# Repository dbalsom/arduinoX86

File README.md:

### About ArduinoX86

I've written a blog article that gives an overview of this project and how it is used.

https://martypc.blogspot.com/2023/06/hardware-validating-emulator.html

This project was originally called Arduino8088, but then I expanded it to support the 8086, 80186, 80286, with plans for
the 80386, so it is now named the suitably generic ArduinoX86.

### Description

This project expands on the basic idea of controlling a CPU via GPIO pins to clock the CPU and read and write control
and data signals. This can be used to validate an emulator's accuracy, but also as a general method of exploring the
operation of CPU instructions and timings.

This project currently supports the following CPUs:

- CMOS variants of the 8088 (Oki, Harris 80C88, etc.)
- AMD D8088
- CMOS variants of the 8086 (Intel 80C86, Harris 80C86)
- NEC V20
- NEC V30
- Intel 80L186
- Harris 80C286
- Intel 80386EX

Where it differs from existing Raspberry Pi-based projects is that it uses an Arduino Giga for the expanded number of
GPIO pins available. The Giga has enough GPIO to operate 808X-compatible CPUs in Maximum mode. This enables several
useful signals to be read such as the QS0 & QS1 processor instruction queue status lines, which give us more insight
into the internal state of the CPU. We can also enable inputs such as READY, NMI, INTR, and TEST, so we can execute
interrupts, NMIs, emulate wait states, and potentially even simulate FPU and DMA operations.

I have been using this project to validate the cycle-accuracy of my PC
emulator, [MartyPC](https://github.com/dbalsom/martypc), and produce CPU test
suites for emulators, covering
the [8088](https://github.com/singleStepTests/8088/), [V20](https://github.com/SingleStepTests/v20)
and [8086](https://github.com/singleStepTests/8086/) and [286](https://github.com/singlesteptests/80286) to date.

This project has three main components:

- The CPU server software, which runs on the Arduino, and establishes a serial protocol to reset the CPU, load and store
  register state, as well as interactively operate the CPU if desired;
- The CPU client software, which runs on your computer and controls the CPU after the CPU server has set up initial
  register state as desired, or uploads an entire program to be run automatically with register state collected at the
  end of execution;
- The CPU socket PCB shields, which seat on top of the Arduino, and provide a physical interface between the CPU and
  GPIO
  lines.

The original "Arduino8088" project utilized an Arduino MEGA, but this board no longer supported.
It is painfully slow and limited to a serial UART instead of fast native USB communication. As of the current
release, an [Arduino Due](https://store.arduino.cc/products/arduino-due), or preferably,
an [Arduino GIGA](https://store.arduino.cc/products/giga-r1-wifi) should be used instead. A GIGA is required to
operate 5V CPUs such as older 80186's and the 80286. Despite Arduino's official warnings, the STM32 GPIO in the Giga is
5V tolerant (with a few exceptions). You will likely void your warranty and I take no responsibility for any damage to
your Arduino that occurs attempting to use a 5V CPU with your Arduino.

### 8088,8086,V20,V30 Support

Revision 1.1 of the 808X shield supports the 8086 and NEC V30 by adding a connection for the 8086's BHE pin.

The Due can operate the 8088, 8086, V20 and V30, despite these chips being 5V. The current 8088 shield feeds those CPUs
3.3V which they tolerate quite well at low clock speeds.

The Giga can operate the 8088, 8086, V20 and V30 directly at 5V if desired. The Giga requires the 3V supply pin to be
cut off the shield's pin headers and external power supplied due to the lower available overall power budget.

> [!WARNING]  
> Do not attempt to use the 8088 shield with a Giga without using external power, or you may damage your Arduino.

### 80186 Support

The ArduinoX86 cpu_server sketch supports operation of a low-voltage 80L186 on an Arduino Due.

There is no shield yet for the 80186, you will need to use a breakout board and connect directly to the Arduino Due's
headers. See [Using an 80186](https://github.com/dbalsom/arduinoX86/wiki/Using-an-80186) for more information.

### 80286 Support

A shield for the 80C286 is in the design phase, located in `/shields/286_5V`

Current support for the 80286 has been performed via breadboard.

### 80386 Support

A shield for the 80386EX CPU is provided in `/shields/386EX_V4`

## Can the CPU be clocked fast enough with an Arduino?

In short, no. We are well past the published minimum cycle times when executing programs via a serial protocol, cycle by
cycle. Some chips tolerate this better than others. When working with an Intel branded 8088, I noticed that effective
address calculations were failing to add the displacement or index register, but otherwise functioned. I have had more
luck with the AMD second-source 8088 CPUs, which seem to function perfectly under slow clocks, although they will hang
and need to be reset if not cycled for a several milliseconds. The issue is "dynamic logic" - logic gates that lose
their state if not refreshed electrically within a frequent enough interval. To be absolutely safe, it is best to use a
fully CMOS process CPU such as the 80C88. CMOS versions of most x86 chips are available.

## To use

An example application for cpu_server is provided, written in Rust, in the `/crates/exec_program` directory. It
demonstrates how to upload arbitrary code to the ArduinoX86 and display cycle traces. The client will emulate the
entire address space and set up a basic IVT.

# Project Structure

## /asm

Assembly language files, intended to be assembled with NASM. To execute code on the ArduinoX86, one must supply two
binary files, one containing the program to be executed, and one containing the register values to load onto the CPU
before program execution.

## /crates/arduinox86_client

A library crate that implements a client for the ArduinoX86's serial protocol.

## /crates/arduinox86_cpu

A library crate built on top of the `arduinox86_client` crate, this provides a `RemoteCpu` struct that models CPU state
and can execute programs.

## /crates/arduinox86_gui

A GUI (written in egui) for ArduinoX86, supporting the 386EX. It allows you to write and assemble assembly-language
programs and execute them on the CPU with an easy-to-use interface.

## /crates/exec_program

A binary implementing an interface for the `arduinox86_cpu` crate that will load a provided register state binary and
execute the specified program binary.

## /crates/test_generator

A program that generates CPU tests for emulator authors.

The [segment limit capture suite](crates/test_generator/SEGMENT_LIMITS.md) adds deterministic
286 and 386EX real and protected mode observations using the same CPU client and server.

### /shields

Contains the KiCad project files and Gerber files for the various ArduinoX86 shields. See the README.md in each shield
directory for more information and BOMs for building each.

### /platformio/ArduinoX86

The main server code that runs on the Arduino Due or GIGA. You must have [platformio](https://platformio.org/) installed
to build and upload the project to your Arduino.

## Archived Directories

### /sketches/cpu_server

The original cpu_server Arduino IDE sketch. Development has since moved to platformio.

### /sketches/run_program

The original sketch for Arduino MEGA only demonstrating how to control an 8088. It does not contain a serial protocol
server - code is run directly from an array defined within the sketch.

# Ordering Boards

- Ordering boards from any of the KiCad projects is extremely simple using PCBWay's KiCad fabrication plugin.
  - From the Plugin and Content Manager, go the Fabrication Plugins tab, find the PCBWay plugin and install.
  - 
  - Open the PCB editor and click the PCBWay Button
  - 
  - A browser window will open to PCBWay's website with the project uploaded and acceptable defaults selected.
  - If you like you can change the board color, or get a nicer finish with gold (ENIG).
  - 
  - You can then proceed to ordering. Part of your purchase goes back to help fund the KiCad project, which is cool.
  - 

# Credits

Inspired by the Pi8088 validator created by Andreas Jonsson as part of the VirtualXT project:

https://github.com/andreas-jonsson/virtualxt/tree/develop/tools/validator/pi8088

# Other Cool Projects

- 8bitforce's Retroshield: https://www.8bitforce.com/projects/retroshield/

- homebrew8088's Raspberry Pi Hat: https://github.com/homebrew8088/pi86

- The Universal Chip Analyser (U. C. A.): https://x86.fr/uca/

- Foxtech's 486 Breadboard Computer: https://www.youtube.com/watch?v=wSiDSdHS2QQ

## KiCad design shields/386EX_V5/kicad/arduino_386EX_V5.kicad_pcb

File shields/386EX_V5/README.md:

# ArduinoX86 386EX Shield V5

- This is the latest shield design for the 386EX CPU. It supports the addition of a 387SX FPU via stacking headers.

- The 386EX is a low-voltage variant of the 386 with a 16-bit data bus, intended for embedded applications.

- This shield is intended to be **only compatible with the Arduino GIGA board**.

### Important power-related notes:

- This shield has external power pins. You may connect a 3.3V or 5V power source to the pins, i.e. via 0.1" / 2.54mm "DuPont" connectors.

- You may find that the CPU runs even without external power. This is due to the CMOS process - many CMOS CPUs can power themselves by sinking current from any input pin. Correct operation in this state is not guaranteed and has not been battle-tested.

### Notes about 386EX CPUs:

- Unsoldered new-old-stock 386EX chips are often available on eBay, but your mileage may vary.

### Other notes:

If using a donor board, a hot plate or hot-air station will be necessary to successfully remove the CPU without damage.

This shield adds new features over the original:

- PEREQ and ERROR pins have been connected to support stacking a 387SX shield,
- The SMI and SMIACT pins have been connected,
- The JTAG pins have been replaced by a 2x4 header, in popular 0.1" / 2.54mm "DuPont" pins,
- The first Asynchronous serial port has been replaced by a 2x5 header (Serial0),
- The first 8 external INTR lines (INTR0-INTR7) have been run out to separate 1x4 headers,
- 7 status LEDs have been added that will report the status of SMIACT, ADS, RD, WR, W/R, C/M and M/IO.

### Improvements (v5.x) over the previous design (v4) include:

- Added ST LDL1117 1A voltage regulator for the 3.3V bus; this enables users to select from a 5V external power source, 5V input via Arduino pin headers, and 3.3V input via the JTAG/debug header.
- Migrated to 4-layer PCB, and migrated most serial and data traces to the 2x internal copper layers.
- Rounded PCB traces for improved data signal integrity.
- Resized silkscreen labels from 1.0mm to 0.8mm and improved layout.
- Improved schematic layout by grouping major components and subsystems together, for easier readability.
- Added standard diodes to protect 5V and 3.3V inputs and busses from accidental back-feeding.
- Added high-resolution renders of board front and back, populated and depopulated, for improved clarity in assembly diagrams.
- Added note about customizing LED current-limiting resistor values per their current and forward voltage.
- Added BOM to this README.
- Added interactive HTML BOM.
- Added schematic and PCB layout `.PDF` files.
- Added `/production` folder with ready-to-fabricate `.zip` file and `.csv` files for communicating with PCB fabrication houses.

### WARNING!
> Successfully assembling this board requires advanced soldering skills. A solder mask, solder paste, and a hot plate are recommended. (Or in a pinch, a high proficiency with drag-soldering techniques.)

### BOM

Note: Interactive HTML bill of materials is available in `./bom/ibom.html`.

| Reference | Value | Footprint | Quantity |
| --------- | ----- | --------- | -------- |
| C3, C4, C5, C6, C7, C8, C9, C10, C11, C12, C13, C14 | 0.1 µF | C_0603 | 12 |
| C1 | 4.7 µF | C_0805 | 1 |
| C2 | 1 µF | C_0805 | 1 |
| R2, R3, R4, R5, R9, R10, R11 | User's TBD | R_0603 | 7 |
| R1, R6, R7, R8, R12, R13, R14, R15 | 3.3 K Ω | R_0603 | 7 |
| D1, D2, D4, D5, D6, D7, D8 | 20mA green |  D_0603 | 7 |
| D3, D9, D10 | S1A-13-F | DIOM5226X240N | 3 |
| U1 | LDL1117S33R | SOT223_STM-M | 1 |
| U2 | ULN2003A | TSSOP-16_4.4x5mm_P0.65mm | 1 |
| U3 | SN74LV14A | TSSOP-14_4.4x5mm_P0.65mm | 1 |
| U4 | AT24CS01-STUM | SOT-23-5 | 1 |
| U5 | I386EX_PQFP | PQFP-132_24x24mm_P0.635mm_i386 | 1 |
| J5, J6, J7 | 4-pin DuPont | PinHeader_1x04_P2.54mm_Vertical | 3 |
| J1, J3 | 3-pin DuPont | PinHeader_1x03_P2.54mm_Vertical | 2 |
| J2 | 2-pin DuPont | PinHeader_1x02_P2.54mm_Vertical | 1 |
| J4 | 2x5-pin DuPont | PinHeader_2x05_P2.54mm_Vertical | 1 |
| J8 | 2x4-pin DuPont | PinHeader_2x04_P2.54mm_Vertical | 1 |

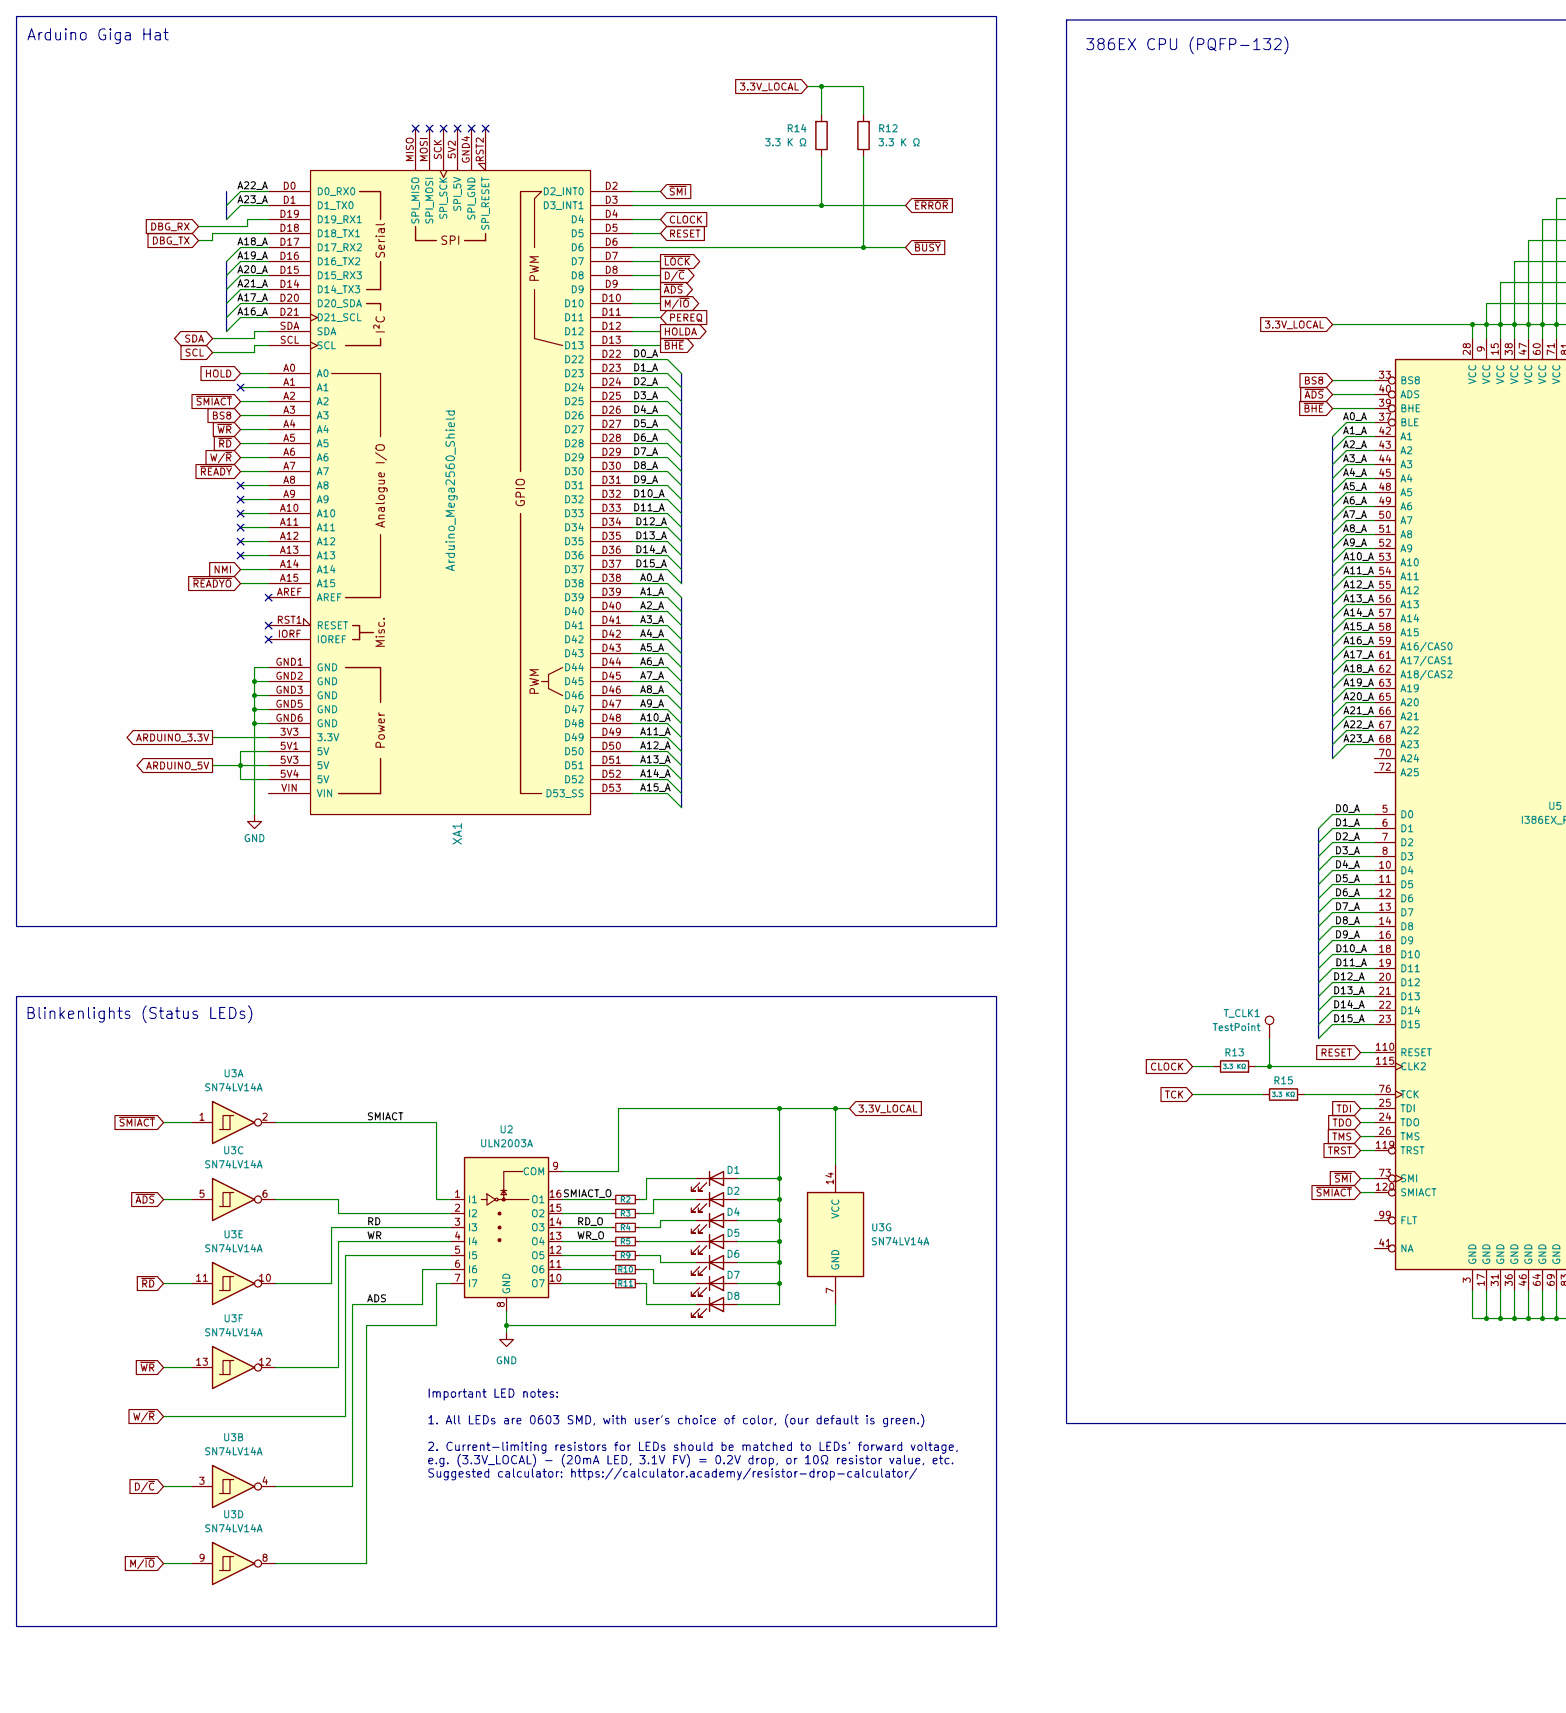
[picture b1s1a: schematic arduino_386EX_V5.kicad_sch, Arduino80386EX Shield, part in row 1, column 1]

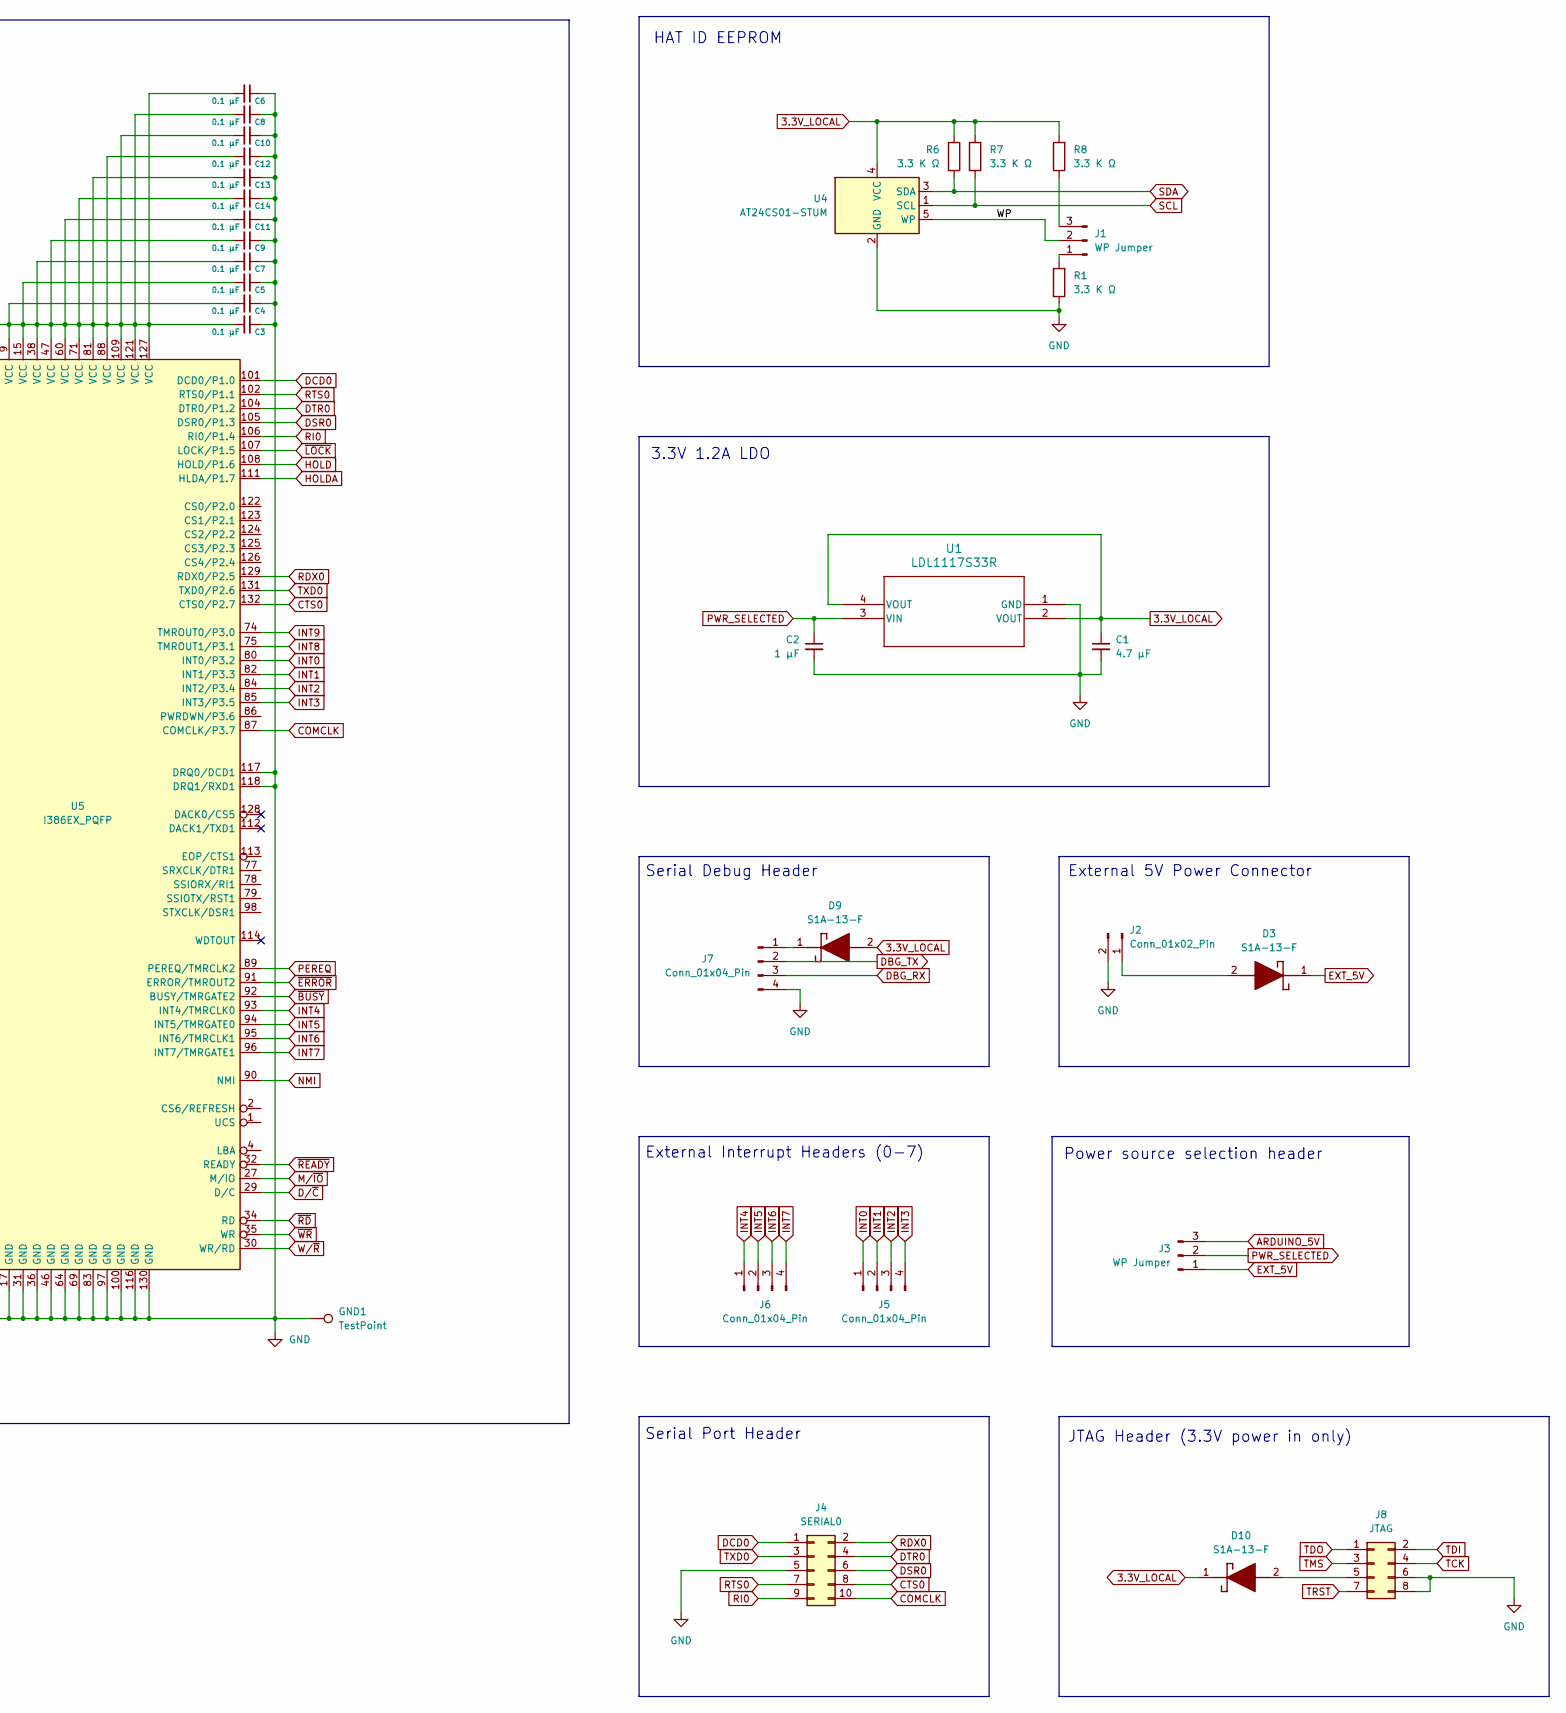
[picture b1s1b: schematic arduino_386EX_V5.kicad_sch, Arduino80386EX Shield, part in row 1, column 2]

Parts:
C1: 4.7 µF; C_0805_2012Metric
C2: 1 µF; C_0805_2012Metric
C3, C4, C5, C6, C7, C8, C9, C10, C11, C12, C13, C14: 0.1 µF; C_0603_1608Metric_Pad1.08x0.95mm_HandSolder
D1, D2, D4, D5, D6, D7, D8: 0603 Green; LED_0603_1608Metric_Pad1.05x0.95mm_HandSolder
D3, D9, D10: S1A-13-F; DIOM5226X240N; Manufacturer_Part_Number S1A-13-F; Mouser Part Number 621-S1A-F
GND1: TestPoint; TestPoint_Pad_D1.0mm
J1, J3: WP Jumper; PinHeader_1x03_P2.54mm_Vertical
J2: Conn_01x02_Pin; PinHeader_1x02_P2.54mm_Vertical
J4: SERIAL0; PinHeader_2x05_P2.54mm_Vertical
J5, J6, J7: Conn_01x04_Pin; PinHeader_1x04_P2.54mm_Vertical
J8: JTAG; PinHeader_2x04_P2.54mm_Vertical
R1, R6, R7, R8, R12, R14: 3.3 K Ω; R_0603_1608Metric_Pad0.98x0.95mm_HandSolder
R2, R3, R4, R5, R9, R10, R11: R_Small; R_0603_1608Metric_Pad0.98x0.95mm_HandSolder
R13, R15: 3.3 KΩ; R_0603_1608Metric_Pad0.98x0.95mm_HandSolder
T_CLK1: TestPoint; TestPoint_Pad_D1.0mm
U1: LDL1117S33R; SOT223_STM-M
U2: ULN2003A; TSSOP-16_4.4x5mm_P0.65mm
U3: SN74LV14A; TSSOP-14_4.4x5mm_P0.65mm
U4: AT24CS01-STUM; SOT-23-5
U5: I386EX_PQFP; PQFP-132_24x24mm_P0.635mm_i386
XA1: Arduino_Mega2560_Shield

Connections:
3.3V_LOCAL: C1.1, C3.2, C4.2, C5.2, C6.2, C7.2, C8.2, C9.2, C10.2, C11.2, C12.2, C13.2, C14.2, D1.2 (A), D2.2 (A), D4.2 (A), D5.2 (A), D6.2 (A), D7.2 (A), D8.2 (A), D9.2 (A), D10.1 (K), R6.2, R7.2, R8.2, R12.2, R14.2, U1.2 (VOUT), U1.4 (VOUT), U2.9 (COM), U3.14 (VCC), U4.4 (VCC), U5.9 (VCC), U5.15 (VCC), U5.28 (VCC), U5.38 (VCC), U5.47 (VCC), U5.60 (VCC), U5.71 (VCC), U5.81 (VCC), U5.88 (VCC), U5.109 (VCC), U5.121 (VCC), U5.127 (VCC)
/A0_A: U5.37 (BLE), XA1.D38
/A1_A: U5.42 (A1), XA1.D39
/A2_A: U5.43 (A2), XA1.D40
/A3_A: U5.44 (A3), XA1.D41
/A4_A: U5.45 (A4), XA1.D42
/A5_A: U5.48 (A5), XA1.D43
/A6_A: U5.49 (A6), XA1.D44
/A7_A: U5.50 (A7), XA1.D45
/A8_A: U5.51 (A8), XA1.D46
/A9_A: U5.52 (A9), XA1.D47
/A10_A: U5.53 (A10), XA1.D48
/A11_A: U5.54 (A11), XA1.D49
/A12_A: U5.55 (A12), XA1.D50
/A13_A: U5.56 (A13), XA1.D51
/A14_A: U5.57 (A14), XA1.D52
/A15_A: U5.58 (A15), XA1.D53 (D53_SS)
/A16_A: U5.59 (A16/CAS0), XA1.D21 (D21_SCL)
/A17_A: U5.61 (A17/CAS1), XA1.D20 (D20_SDA)
/A18_A: U5.62 (A18/CAS2), XA1.D17 (D17_RX2)
/A19_A: U5.63 (A19), XA1.D16 (D16_TX2)
/A20_A: U5.65 (A20), XA1.D15 (D15_RX3)
/A21_A: U5.66 (A21), XA1.D14 (D14_TX3)
/A22_A: U5.67 (A22), XA1.D0 (D0_RX0)
/A23_A: U5.68 (A23), XA1.D1 (D1_TX0)
/ADS: U2.6 (I6), U3.4
/D0_A: U5.5 (D0), XA1.D22
/D1_A: U5.6 (D1), XA1.D23
/D2_A: U5.7 (D2), XA1.D24
/D3_A: U5.8 (D3), XA1.D25
/D4_A: U5.10 (D4), XA1.D26
/D5_A: U5.11 (D5), XA1.D27
/D6_A: U5.12 (D6), XA1.D28
/D7_A: U5.13 (D7), XA1.D29
/D8_A: U5.14 (D8), XA1.D30
/D9_A: U5.16 (D9), XA1.D31
/D10_A: U5.18 (D10), XA1.D32
/D11_A: U5.19 (D11), XA1.D33
/D12_A: U5.20 (D12), XA1.D34
/D13_A: U5.21 (D13), XA1.D35
/D14_A: U5.22 (D14), XA1.D36
/D15_A: U5.23 (D15), XA1.D37
/RD: U2.3 (I3), U3.10
/RD_O: R4.1, U2.14 (O3)
/SMIACT: U2.1 (I1), U3.2
/SMIACT_O: R2.1, U2.16 (O1)
/WP: J1.2, U4.5 (WP)
/WR: U2.4 (I4), U3.12
/WR_O: R5.1, U2.13 (O4)
ARDUINO_3.3V: XA1.3V3 (3.3V)
ARDUINO_5V: J3.3, XA1.5V1 (5V), XA1.5V3 (5V), XA1.5V4 (5V)
BS8: U5.33 (BS8), XA1.A3
CLOCK: R13.1, XA1.D4
COMCLK: J4.10, U5.87 (COMCLK/P3.7)
CTS0: J4.8, U5.132 (CTS0/P2.7)
DBG_RX: J7.3, XA1.D19 (D19_RX1)
DBG_TX: J7.2, XA1.D18 (D18_TX1)
DCD0: J4.1, U5.101 (DCD0/P1.0)
DSR0: J4.6, U5.105 (DSR0/P1.3)
DTR0: J4.4, U5.104 (DTR0/P1.2)
D/~C: U3.3, U5.29 (D/C), XA1.D8
EXT_5V: D3.1 (K), J3.1
GND: C1.2, C2.2, C3.1, C4.1, C5.1, C6.1, C7.1, C8.1, C9.1, C10.1, C11.1, C12.1, C13.1, C14.1, GND1.1, J2.2, J4.5, J7.4, J8.6, J8.8, R1.1, U1.1 (GND), U2.8 (GND), U3.7 (GND), U4.2 (GND), U5.3 (GND), U5.17 (GND), U5.31 (GND), U5.36 (GND), U5.46 (GND), U5.64 (GND), U5.69 (GND), U5.83 (GND), U5.97 (GND), U5.100 (GND), U5.116 (GND), U5.117 (DRQ0/DCD1), U5.118 (DRQ1/RXD1), U5.130 (GND), XA1.GND1 (GND), XA1.GND2 (GND), XA1.GND3 (GND), XA1.GND5 (GND), XA1.GND6 (GND); also elsewhere on the board
HOLD: U5.108 (HOLD/P1.6), XA1.A0
HOLDA: U5.111 (HLDA/P1.7), XA1.D12
INT0: J5.1, U5.80 (INT0/P3.2)
INT1: J5.2, U5.82 (INT1/P3.3)
INT2: J5.3, U5.84 (INT2/P3.4)
INT3: J5.4, U5.85 (INT3/P3.5)
INT4: J6.1, U5.93 (INT4/TMRCLK0)
INT5: J6.2, U5.94 (INT5/TMRGATE0)
INT6: J6.3, U5.95 (INT6/TMRCLK1)
INT7: J6.4, U5.96 (INT7/TMRGATE1)
INT8: U5.75 (TMROUT1/P3.1)
INT9: U5.74 (TMROUT0/P3.0)
M/~IO: U3.9, U5.27 (M/IO), XA1.D10
NMI: U5.90 (NMI), XA1.A14
unnamed: D1.1 (K), R2.2
unnamed: D2.1 (K), R3.2
unnamed: D3.2 (A), J2.1
unnamed: D4.1 (K), R4.2
unnamed: D5.1 (K), R5.2
unnamed: D6.1 (K), R9.2
unnamed: D7.1 (K), R10.2
unnamed: D8.1 (K), R11.2
unnamed: D9.1 (K), J7.1
unnamed: D10.2 (A), J8.5
unnamed: J1.1, R1.2
unnamed: J1.3, R8.1
unnamed: U2.2 (I2), U3.6
unnamed: U2.7 (I7), U3.8
unnamed: R3.1, U2.15 (O2)
unnamed: R9.1, U2.12 (O5)
unnamed: R10.1, U2.11 (O6)
unnamed: R11.1, U2.10 (O7)
unnamed: R13.2, T_CLK1.1, U5.115 (CLK2)
unnamed: R15.2, U5.76 (TCK)
PEREQ: U5.89 (PEREQ/TMRCLK2), XA1.D11
PWR_SELECTED: C2.1, J3.2, U1.3 (VIN)
RDX0: J4.2, U5.129 (RDX0/P2.5)
RESET: U5.110 (RESET), XA1.D5
RI0: J4.9, U5.106 (RI0/P1.4)
RTS0: J4.7, U5.102 (RTS0/P1.1)
SCL: R7.1, U4.1 (SCL), XA1.SCL
SDA: R6.1, U4.3 (SDA), XA1.SDA
TCK: J8.4, R15.1
TDI: J8.2, U5.25 (TDI)
TDO: J8.1, U5.24 (TDO)
TMS: J8.3, U5.26 (TMS)
TRST: J8.7, U5.119 (TRST)
TXD0: J4.3, U5.131 (TXD0/P2.6)
W/~R: U2.5 (I5), U5.30 (WR/RD), XA1.A6
~ADS: U3.5, U5.40 (ADS), XA1.D9
~BHE: U5.39 (BHE), XA1.D13
~BUSY: R12.1, U5.92 (BUSY/TMRGATE2), XA1.D6
~ERROR: R14.1, U5.91 (ERROR/TMROUT2), XA1.D3 (D3_INT1)
~LOCK: U5.107 (LOCK/P1.5), XA1.D7
~RD: U3.11, U5.34 (RD), XA1.A5
~READYO: XA1.A15
~READY: U5.32 (READY), XA1.A7
~SMIACT: U3.1, U5.120 (SMIACT), XA1.A2
~SMI: U5.73 (SMI), XA1.D2 (D2_INT0)
~WR: U3.13, U5.35 (WR), XA1.A4

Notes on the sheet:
Power source selection header
Serial Port Header
JTAG Header (3.3V power in only)
Blinkenlights (Status LEDs)
HAT ID EEPROM
External 5V Power Connector
Serial Debug Header
External Interrupt Headers (0-7)
3.3V 1.2A LDO
386EX CPU (PQFP-132)
Arduino Giga Hat
Important LED notes: 1. All LEDs are 0603 SMD, with user's choice of color, (our default is green.) 2. Current-limiting resistors for LEDs should be matched to LEDs' forward voltage, e.g. (3.3V_LOCAL) - (20mA LED, 3.1V FV) = 0.2V drop, or 10Ω resistor value, etc. Suggested calculator: https://calcu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

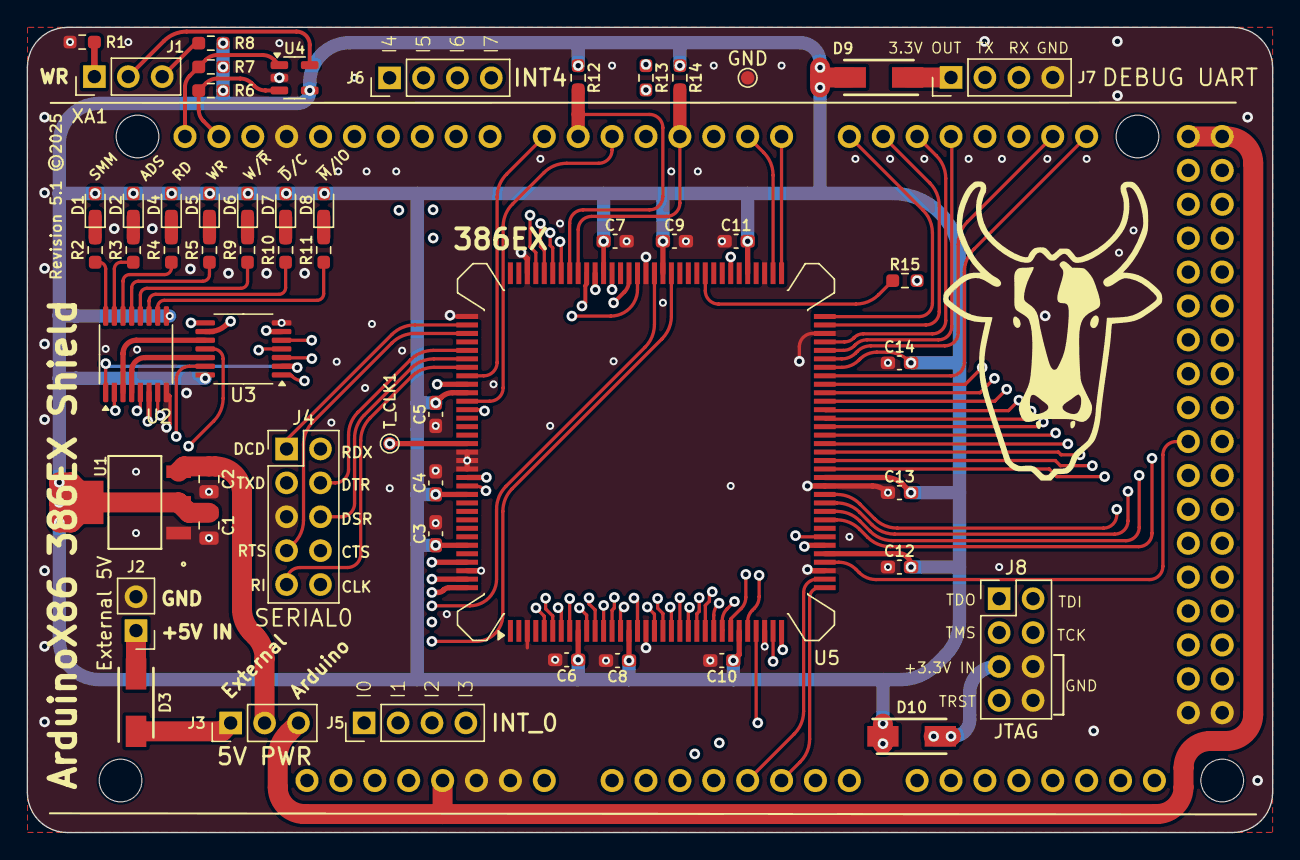
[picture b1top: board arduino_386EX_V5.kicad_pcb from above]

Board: 4 copper layers, 93.3 x 60.3 mm, 55 parts (0 on the bottom side), 119 nets.

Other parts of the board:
GND: TestPoint; TestPoint_Pad_D1.0mm

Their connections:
GND: GND.1; also elsewhere on the board

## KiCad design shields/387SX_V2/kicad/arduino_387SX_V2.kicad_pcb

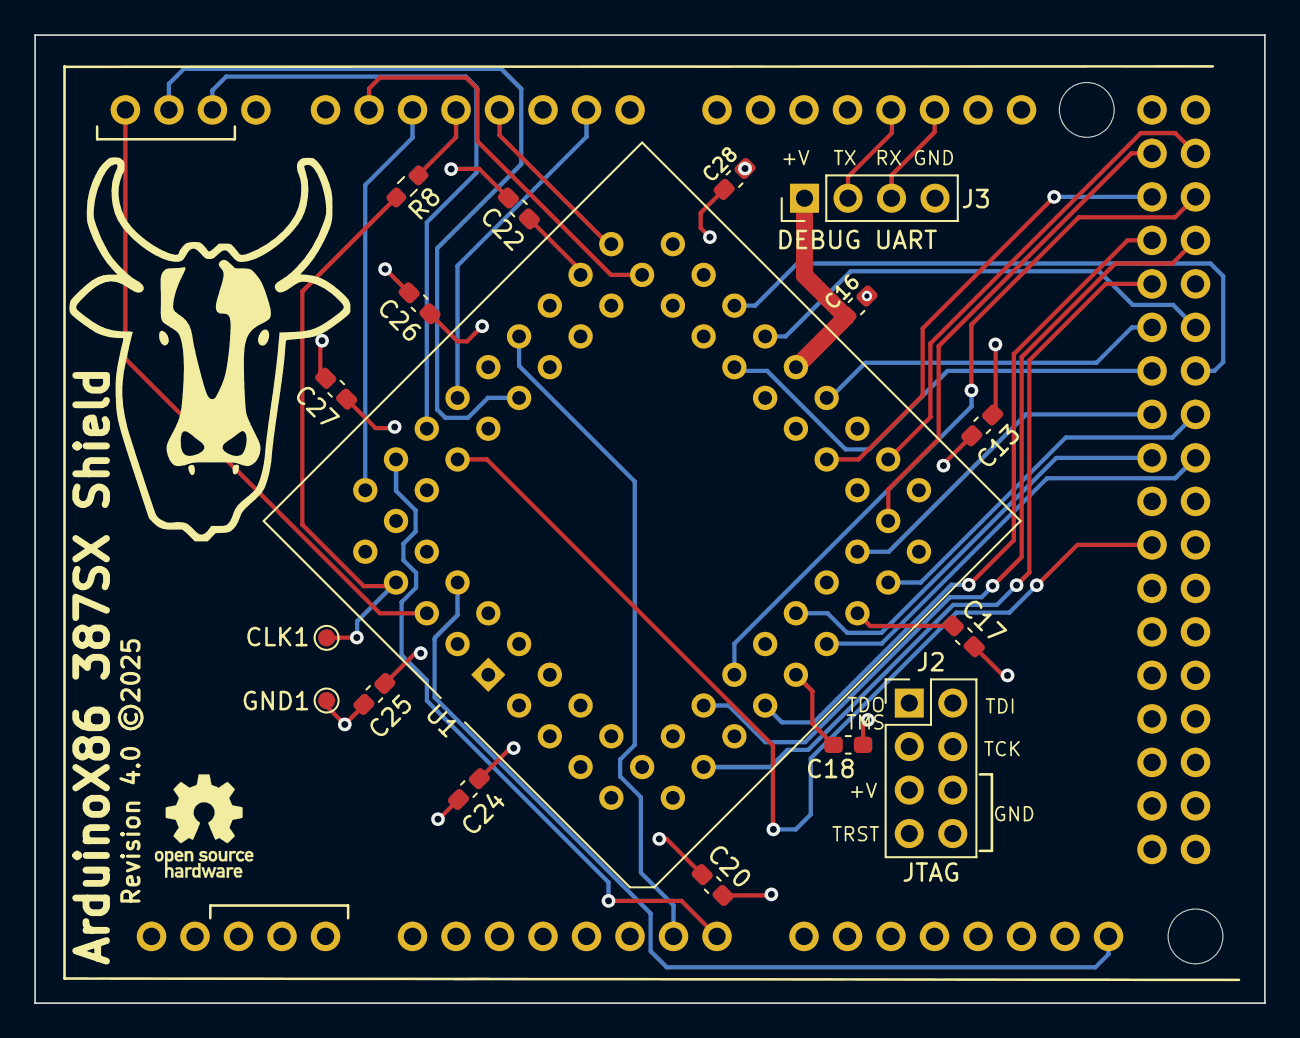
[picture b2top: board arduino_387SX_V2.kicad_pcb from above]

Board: 4 copper layers, 71.8 x 56.5 mm, 18 parts (0 on the bottom side), 33 nets.

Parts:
C13, C16, C17, C18, C20, C22, C24, C25, C26, C27, C28: C; C_0603_1608Metric_Pad1.08x0.95mm_HandSolder
CLK1: TestPoint; TestPoint_Pad_D1.0mm
GND1: TestPoint; TestPoint_Pad_D1.0mm
J2: JTAG; PinHeader_2x04_P2.54mm_Vertical
J3: Conn_01x04_Pin; PinHeader_1x04_P2.54mm_Vertical
R8: R; R_0603_1608Metric_Pad0.98x0.95mm_HandSolder
U1: PLCC-68_286-THT-Socket
XA1: Arduino_Mega2560_Shield

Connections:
+3.3VP: C13.2, C16.2, C17.2, C18.2, C20.2, C22.2, C24.2, C25.2, C26.2, C27.2, C28.2, J2.5, J3.1, U1.4 (Vcc), U1.9 (Vcc), U1.13 (Vcc), U1.22 (Vcc), U1.26 (Vcc), U1.31 (Vcc), U1.33 (Vcc), U1.37 (Vcc), U1.39 (Vcc), U1.40 (STEN), U1.43 (Vcc), U1.46 (Vcc), U1.50 (Vcc), U1.58 (Vcc), U1.59 (CKM), U1.62 (Vcc), U1.64 (Vcc)
/A2_A: U1.48 (~CMD0), XA1.D40
/A23_A: U1.45 (NPS2), XA1.D1 (D1_TX0)
/D0_A: U1.19 (D00), XA1.D22
/D1_A: U1.20 (D01), XA1.D23
/D2_A: U1.23 (D02), XA1.D24
/D3_A: U1.8 (D03), XA1.D25
/D4_A: U1.7 (D04), XA1.D26
/D5_A: U1.6 (D05), XA1.D27
/D6_A: U1.3 (D06), XA1.D28
/D7_A: U1.2 (D07), XA1.D29
/D8_A: U1.24 (D08), XA1.D30
/D9_A: U1.28 (D09), XA1.D31
/D10_A: U1.29 (D10), XA1.D32
/D11_A: U1.30 (D11), XA1.D33
/D12_A: U1.16 (D12), XA1.D34
/D13_A: U1.15 (D13), XA1.D35
/D14_A: U1.12 (D14), XA1.D36
/D15_A: U1.11 (D15), XA1.D37
CLOCK: R8.1, XA1.D4
DBG_RX: J3.3, XA1.D19 (D19_RX1)
DBG_TX: J3.2, XA1.D18 (D18_TX1)
GND: C13.1, C16.1, C17.1, C18.1, C20.1, C22.1, C24.1, C25.1, C26.1, C27.1, C28.1, GND1.1, J2.6, J2.8, J3.4, U1.5 (Vss), U1.14 (Vss), U1.21 (Vss), U1.25 (Vss), U1.27 (Vss), U1.32 (Vss), U1.34 (Vss), U1.38 (Vss), U1.42 (Vss), U1.53 (NUMCLK2), U1.55 (Vss), U1.60 (Vss), U1.61 (Vss), U1.63 (Vss), U1.66 (Vss), XA1.GND2 (GND), XA1.GND3 (GND), XA1.GND5 (GND), XA1.GND6 (GND)
M/~IO: U1.44 (~NPS1), XA1.D10
unnamed: CLK1.1, R8.2, U1.54 (CPUCLK2)
PEREQ: U1.56 (PEREQ), XA1.D11
RESET: U1.51 (RESETIN), XA1.D5
W/~R: U1.41 (W/~R), XA1.A6
~ADS: U1.47 (~ADS), XA1.D9
~BUSY: U1.36 (~BUSY), XA1.D6
~ERROR: U1.35 (~ERROR), XA1.D3 (D3_INT1)
~READYO: U1.57 (~READY0), XA1.A15
~READY: U1.49 (~READY), XA1.A7

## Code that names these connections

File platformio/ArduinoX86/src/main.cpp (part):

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      cycle_state.pins |= CycleState::ALE;
    }
    if (Controller.readBHEPin()) {
      cycle_state.pins |= CycleState::BHE;
    }
    if (Controller.readLockPin()) {
      cycle_state.pins |= CycleState::LOCK;
    }
    if (Controller.readReadyPin()) {
      cycle_state.pins |= CycleState::READY;
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
      if (CPU.loadall_checkpoint == 0 && (CPU.address_latch() == SMM_LOAD_CHECKPOINT)) {
        Controller.getBoard().debugPrintf(DebugType::LOAD, false, "## LOAD_SMM_386: Passed checkpoint. Deasserting SMI. Next fetch should be for program\n\r");
        Controller.writePin(OutputPin::Smi, true); // SMI is active-low
        CPU.loadall_checkpoint = 1;
      }
    }
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
  if (CPU.bus_state == HALT) {
    Controller.getBoard().debugPrintln(DebugType::EXECUTE, "## EXECUTE: HALT detected - Ending program execution.");
    Controller.writePin(OutputPin::Nmi, true);

    if (CPU.cpu_type != CpuType::i80386) {
      // The 386 keeps a persistent HALT bus state, so we can't return or we'll never escape it.
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    // Use checkpoint "1" to specify that NMI has been detected. This just prevents the debug message from
    // printing every cycle after NMI.
    if (CPU.nmi_checkpoint == 0) {
      Controller.getBoard().debugPrintln(DebugType::EXECUTE, "## EXECUTE: NMI pin high - Execute will end at IVT fetch.");
      CPU.nmi_checkpoint = 1;
    }
  }
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  if (!READ_SMI_PIN) {
    Controller.getBoard().debugPrintln(DebugType::EXECUTE, "## EXECUTE: SMI asserted.");
    // Sometimes the bus is PASV[1] on 386 during ADS. Not sure why.
    Controller.getBoard().debugPrintf(DebugType::EXECUTE, false, "## EXECUTE: SMI asserted, ads is %s, bus state is %d\n\r", Controller.readALEPin() ? "high" : "low", (CPU.status0 & 0xF));
    if (Controller.readALEPin() && ((CPU.bus_state == MEMW) || ((CPU.status0 & 0xF) == 1))) {

      Controller.getBoard().debugPrintln(DebugType::EXECUTE, "## EXECUTE: ALE high and MEMW cycle detected.");
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  if ((READ_NMI_PIN) && (CPU.nmi_checkpoint == 0)) {
    // Use checkpoint "1" to specify that NMI has been detected. This just prevents the debug message from
    // printing every cycle after NMI.
    Controller.getBoard().debugPrintln(DebugType::EXECUTE, "## EXECUTE: NMI pin high - Execute will end at IVT fetch.", true);
    CPU.nmi_checkpoint = 1;
    ArduinoX86::CycleLogger->disable_logging();
  }
  else if ((!READ_SMI_PIN) && (CPU.smi_checkpoint == 0)) {
    Controller.getBoard().debugPrintln(DebugType::ERROR, "## EXECUTE: SMI pin asserted - Execute will end at SMRAM write.", true);
    CPU.smi_checkpoint = 1;
    ArduinoX86::CycleLogger->disable_logging();
  }
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      if (CPU.use_smm()) {
        Controller.getBoard().debugPrintln(DebugType::EXECUTE, "## EXECUTE: HALT with SMM enabled.");
        if (READ_SMI_PIN) {
          Controller.getBoard().debugPrintln(DebugType::EXECUTE, "## EXECUTE: HALT - Writing SMI pin low", true);
          //Controller.writePin(OutputPin::Ready, true);
          Controller.writePin(OutputPin::Smi, false);
        }
      }
      else {
        Controller.getBoard().debugPrintln(DebugType::EXECUTE, "## EXECUTE: HALT with SMM disabled.");
        if (!READ_NMI_PIN){
          Controller.getBoard().debugPrintln(DebugType::EXECUTE, "## EXECUTE: HALT - Writing NMI pin high.", true);
          Controller.writePin(OutputPin::Nmi, true);
        }
      }
    }
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        Controller.writeDataBus(CPU.data_bus, CPU.data_width);

        if (CPU.nmi_checkpoint == 1 && CPU.address_latch() == 0x0000A) {
          Controller.getBoard().debugPrintln(DebugType::EXECUTE, "## EXECUTE_FINALIZE: Read of NMI IVT with NMI pin high - Resetting STORE PC");
          CPU.nmi_checkpoint = 2;
          CPU.data_bus_resolved = true;
          CPU.s_pc = 0;
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
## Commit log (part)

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2026-03-07 update gitignore

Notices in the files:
platformio/ArduinoX86/src/main.cpp:
ArduinoX86 Copyright 2022-2025 Daniel Balsom
shields/386EX_V5/kicad/arduino_386EX_V5.kicad_pcb:
Revision 5.1 ©2025
shields/387SX_V2/kicad/arduino_387SX_V2.kicad_pcb:
Revision 4.0 ©2025
